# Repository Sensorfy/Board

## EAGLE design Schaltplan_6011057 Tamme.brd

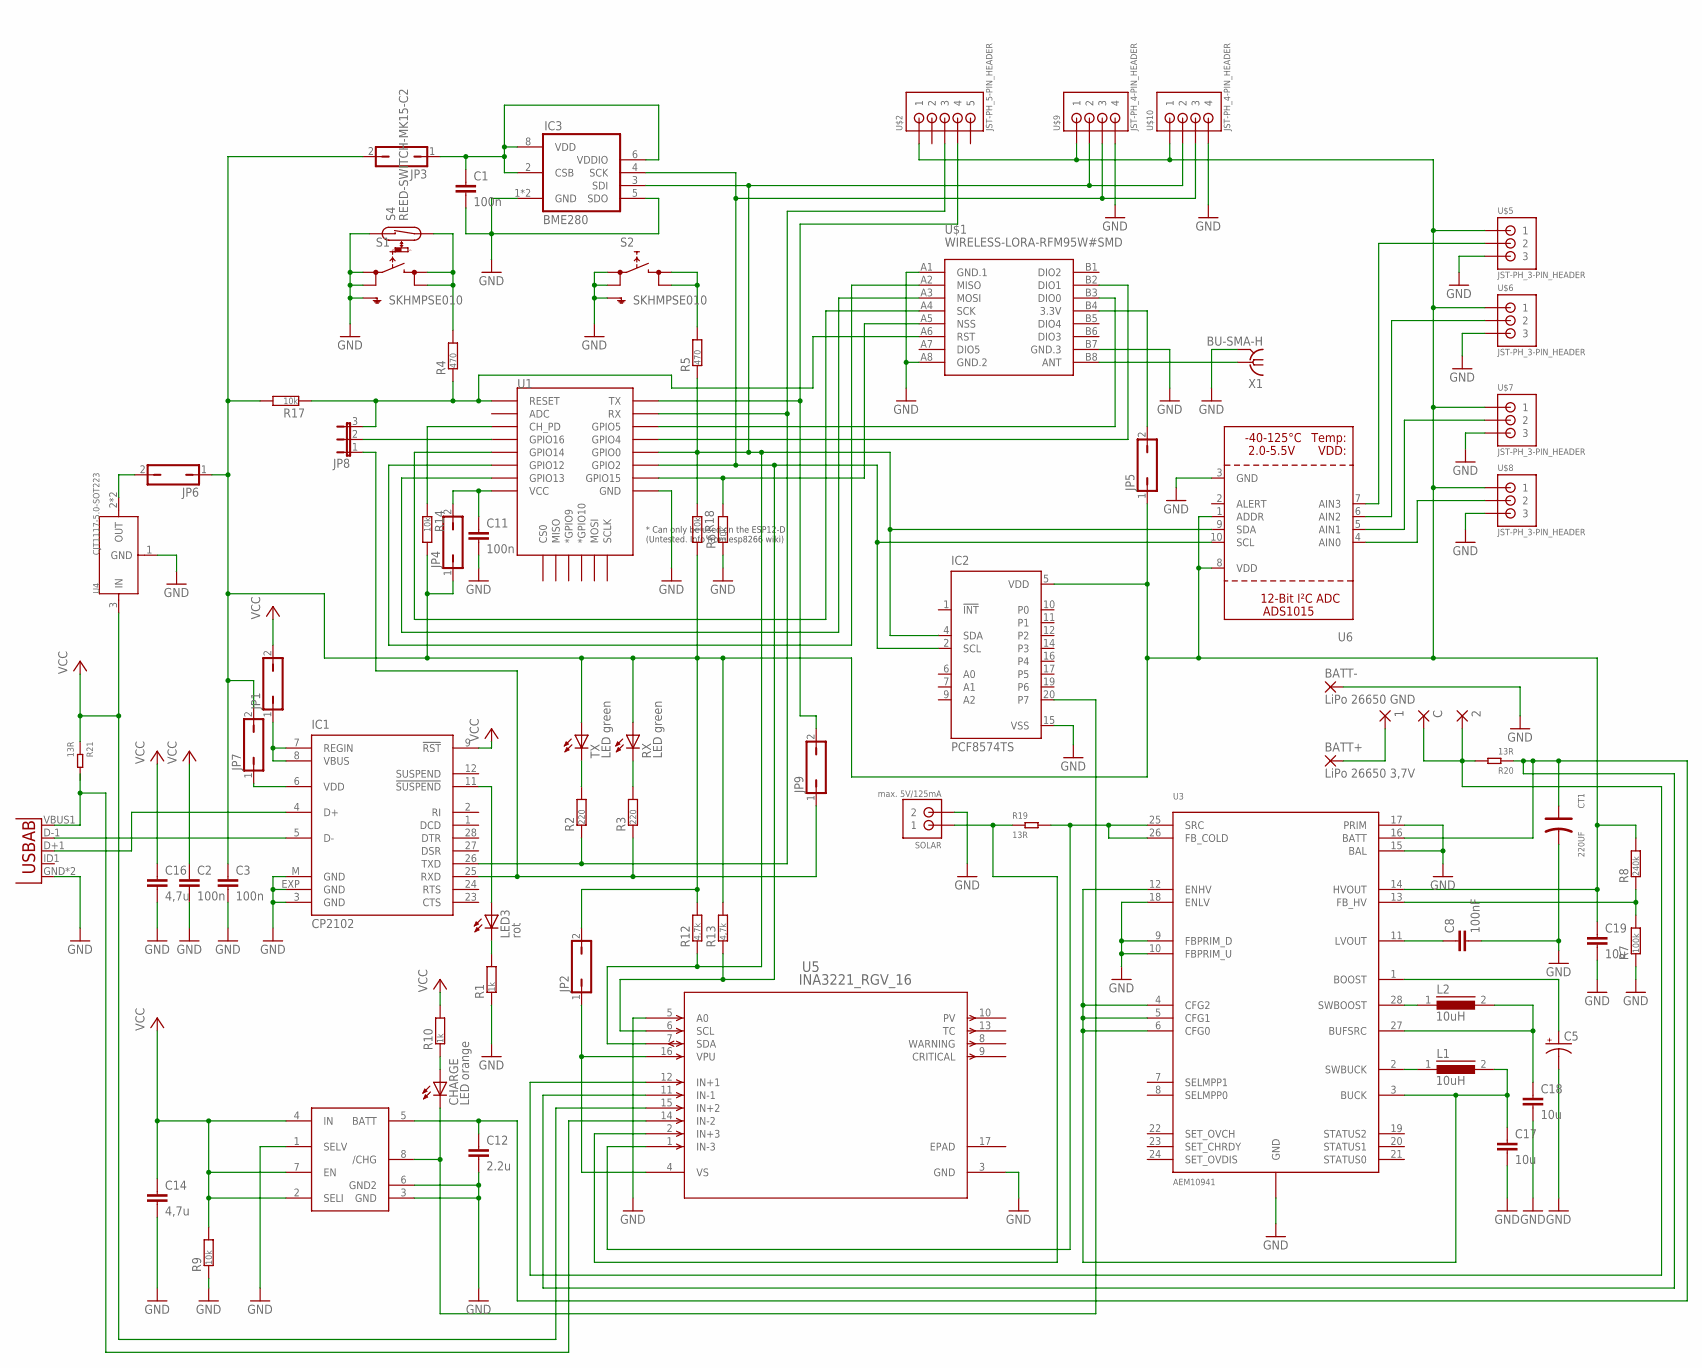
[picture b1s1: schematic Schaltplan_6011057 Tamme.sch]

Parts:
1, 2: WIREPAD2,54/1,0; 2,54/1,0
BATT+: LiPo 26650 3,7V; 4,16O1,6
BATT-: LiPo 26650 GND; 4,16O1,6
C: WIREPAD2,54/1,0; 2,54/1,0
C1, C2, C3, C11: 100n; RESC0805_M
C5: CPOL-USB/3528-21W; B/3528-21W
C8: 100nF; C1206
C12: 2.2u; C1812
C14, C16: 4,7u; C1812
C17, C18, C19: 10u; C1812
CHARGE: LED orange; 1206
CT1: 220UF; ELECTRO-SMD-C-6MM
IC1: CP2102; MLP28
IC2: PCF8574TS; SSOP20
IC3: BME280
JP1, JP2, JP3, JP4, JP5, JP6, JP7, JP9: JP1Q; JP1
JP8: JP2E; JP2
L1, L2: 10uH; DR74
LED3: rot; 1206
R1, R10: 1k; RESC0805_M
R2, R3: 220; RESC0805_M
R4, R5: 470; RESC0805_M
R6, R9, R14, R17, R18: 10k; RESC0805_M
R7: 100k; RESC0805_M
R8: 240k; RESC0805_M
R12, R13: 4,7k; RESC0805_M
R19, R20, R21: 13R; R1206
RX: LED green; 1206
S1, S2: SKHMPSE010; SKHMPXE010
S4: REED-SWITCH-MK15-C2; MK15
SOLAR: max. 5V/125mA; JST_B2B-PH_HEADER
TX: LED green; 1206
U1: ESP12ESMD; ESP12E-SMD
U2: USB""; USB-MICRO-SMD
U3: AEM10941; QFN28_5X5_05PITCH
U4: CJT1117-5.0-SOT223; SOT-223
U5: INA3221_RGV_16; RGV16_2P16X2P16
U6: ADC_ADS1015; MSOP10
U$1: WIRELESS-LORA-RFM95W#SMD
U$2: JST-PH_5-PIN_HEADER; JST_B5B-PH_HEADER
U$3: MAX1811SO8; SO08
U$5, U$6, U$7, U$8: JST-PH_3-PIN_HEADER; JST_B3B-PH_HEADER
U$9, U$10: JST-PH_4-PIN_HEADER; JST_B4B-PH_HEADER
X1: BU-SMA-H

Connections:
3.3V: C3.1, C19.1, IC2.5 (VDD), JP2.2, JP3.2, JP4.1, JP5.1, JP6.1, JP7.2, R8.2, R12.2, R13.2, R14.2, R17.2, R18.2, RX.A, TX.A, U3.14 (HVOUT), U6.1 (ADDR), U6.8 (VDD), U$2.P1 (1), U$5.P1 (1), U$6.P1 (1), U$7.P1 (1), U$8.P1 (1), U$9.P1 (1), U$10.P1 (1)
GND: BATT-.1, C1.2, C2.2, C3.2, C5.-, C8.2, C11.2, C12.2, C14.2, C16.2, C17.2, C18.2, C19.2, CT1.-, IC1.3 (GND), IC1.EXP (GND), IC1.M (GND), IC2.15 (VSS), IC3.1 (GND), IC3.5 (SDO), IC3.7 (GND), R1.1, R6.1, R7.1, R9.1, S1.1 (1.1), S1.2 (1.2), S1.5 (SH), S2.1 (1.1), S2.2 (1.2), S2.5 (SH), S4.1, SOLAR.P2 (2), U1.GND, U2.GND, U2.GND1 (GND), U3.9 (FBPRIM_D), U3.10 (FBPRIM_U), U3.15 (BAL), U3.17 (PRIM), U3.18 (ENLV), U3.GND, U3.GND1 (GND), U3.GND2 (GND), U3.GND3 (GND), U3.GND4 (GND), U3.GND5 (GND), U4.1 (GND), U5.3 (GND), U5.5 (A0), U6.3 (GND), U$1.A1 (GND.1), U$1.A8 (GND.2), U$1.B7 (GND.3), U$3.1 (SELV), U$3.3 (GND), U$3.6 (GND2), U$5.P3 (3), U$6.P3 (3), U$7.P3 (3), U$8.P3 (3), U$9.P4 (4), U$10.P4 (4), X1.2, X1.3 (2), X1.4 (2), X1.5 (2)
unnamed: U$1.B8 (ANT), X1.1
unnamed: R6.2, U1.GPIO15, U$1.A5 (NSS)
unnamed: R4.2, S1.3 (2.1), S1.4 (2.2), S4.2
unnamed: JP8.3, R4.1, R17.1, U1.RESET, U$1.A6 (RST)
unnamed: IC1.4 (D+), U2.D+1 (D+)
unnamed: IC1.5 (D-), U2.D-1 (D-)
unnamed: JP8.2, U1.GPIO16
unnamed: LED3.C, R1.2
unnamed: IC1.25 (RXD), JP8.1, JP9.1, R3.1
unnamed: IC1.26 (TXD), R2.1, U1.RXD0 (RX), U$2.P3 (3)
unnamed: IC1.11 (!SUSPEND), LED3.A
unnamed: R2.2, TX.C
unnamed: R3.2, RX.C
unnamed: R5.2, S2.3 (2.1), S2.4 (2.2)
unnamed: U1.GPIO12, U$1.A2 (MISO)
unnamed: U1.GPIO14, U$1.A4 (SCK)
unnamed: C12.1, CT1.+, R20.1, U3.16 (BATT), U5.11 (IN-1), U$3.5 (BATT)
unnamed: U1.GPIO13, U$1.A3 (MOSI)
unnamed: JP9.2, U1.TXD0 (TX), U$2.P4 (4)
unnamed: JP6.2, U4.2 (OUT), U4.TER (OUT)
unnamed: U6.4 (AIN0), U$8.P2 (2)
unnamed: C17.1, L1.2, U3.3 (BUCK), U3.4 (CFG2), U3.5 (CFG1), U3.6 (CFG0), U3.12 (ENHV)
unnamed: C5.+, U3.1 (BOOST)
unnamed: C18.1, L2.2, U3.27 (BUFSRC)
unnamed: R7.2, R8.1, U3.13 (FB_HV)
unnamed: C1.1, IC3.2 (CSB), IC3.6 (VDDIO), IC3.8 (VDD), JP3.1
unnamed: IC2.4 (SDA), IC3.3 (SDI), R5.1, R12.1, R18.1, U1.GPIO0, U5.7 (SDA), U6.9 (SDA), U$9.P2 (2), U$10.P2 (2)
unnamed: IC2.2 (SCL), IC3.4 (SCK), R13.1, U1.GPIO2, U5.6 (SCL), U6.10 (SCL), U$9.P3 (3), U$10.P3 (3)
unnamed: C8.1, U3.11 (LVOUT)
unnamed: 2.1, C.1, R20.2, U5.12 (IN+1)
unnamed: U6.5 (AIN1), U$7.P2 (2)
unnamed: U6.6 (AIN2), U$6.P2 (2)
unnamed: U6.7 (AIN3), U$5.P2 (2)
unnamed: R19.1, SOLAR.P1 (1), U5.2 (IN+3)
unnamed: CHARGE.C, IC2.20 (P7), U$3.8 (/CHG)
unnamed: CHARGE.A, R10.1
unnamed: R19.2, U3.25 (SRC), U3.26 (FB_COLD), U5.1 (IN-3)
unnamed: U2.VBUS1 (VBUS), U5.14 (IN-2)
unnamed: IC1.7 (REGIN), IC1.8 (VBUS), JP1.1
unnamed: C11.1, JP4.2, U1.VCC
unnamed: JP2.1, U5.4 (VS), U5.16 (VPU)
unnamed: JP5.2, U$1.B4 (3.3V)
unnamed: U1.GPIO4, U$1.B2 (DIO1)
unnamed: U1.GPIO5, U$1.B3 (DIO0)
unnamed: L2.1, U3.28 (SWBOOST)
unnamed: L1.1, U3.2 (SWBUCK)
unnamed: R14.1, U1.CH_PD
unnamed: IC1.6 (VDD), JP7.1
unnamed: 1.1, BATT+.1
VCC: C2.1, C14.1, C16.1, IC1.9 (!RST), JP1.2, R9.2, R10.2, R21.1, U4.3 (IN), U5.15 (IN+2), U$3.2 (SELI), U$3.4 (IN), U$3.7 (EN)

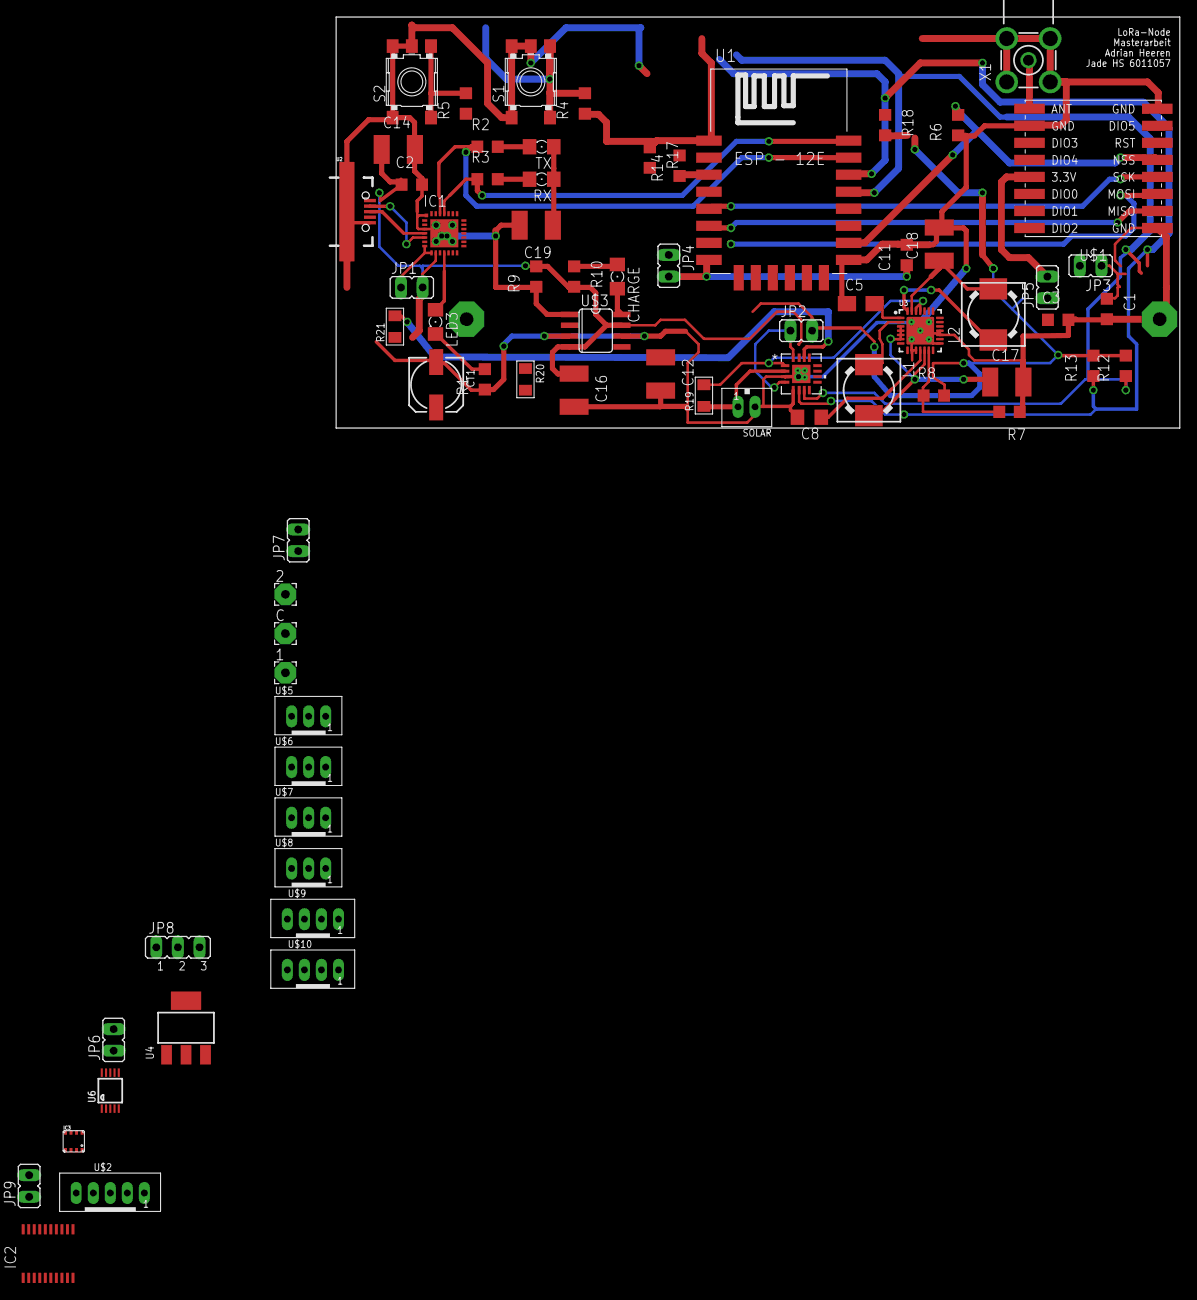
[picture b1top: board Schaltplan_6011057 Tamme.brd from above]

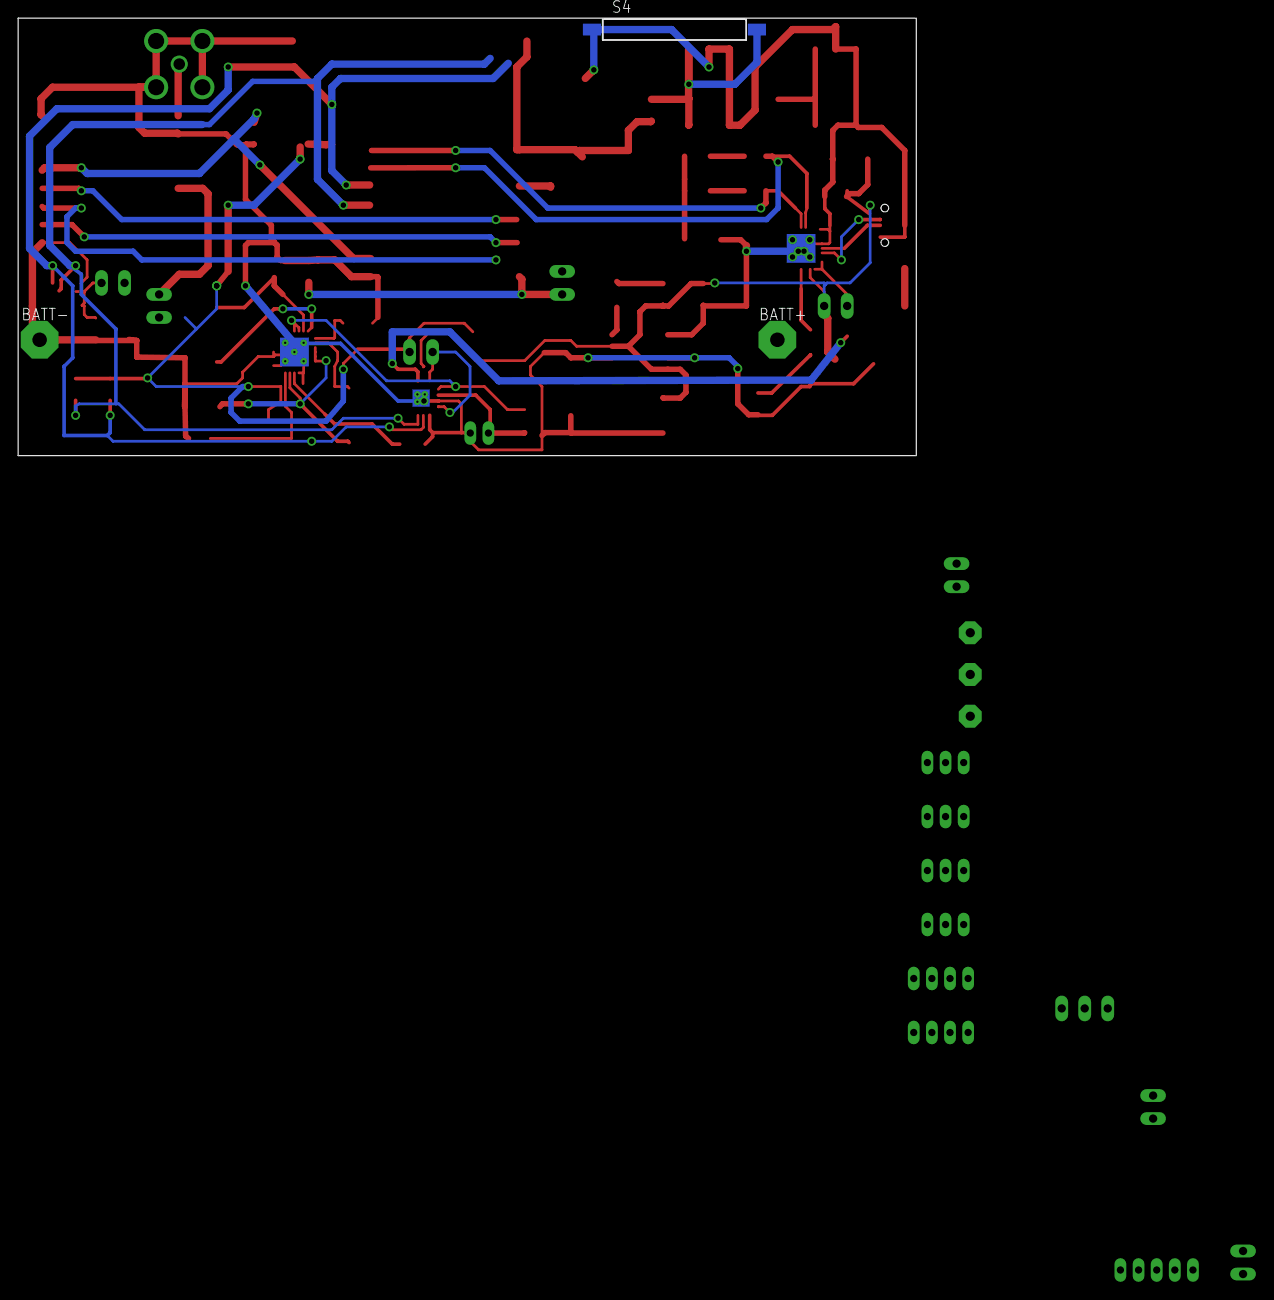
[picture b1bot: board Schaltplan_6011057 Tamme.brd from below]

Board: 2 copper layers, 99.0 x 48.2 mm, 74 parts (3 on the bottom side), 52 nets.

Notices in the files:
parts and their libraries:
diy-modules: Released under the Creative Commons Attribution 4.0 International License: http://creativecommons.org/licenses/by/4.0
microbuilder: This work is placed in the public domain, and may be freely used for commercial and non-commercial work with the following conditions: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
